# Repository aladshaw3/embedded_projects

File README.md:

## Personal Embedded Projects
Mono Repo for various personal embedded projects with my husband

This mono repo is strictly just for code development with a lot of boilerplate for helping
to write unit tests for the code. Does not include build instructions for specific devices.

# Getting Started

(1) Initial Setup

```bash
make environment
make grab-submodules
```

NOTE: Not strictly required if you have an environment that is already setup. See build/setup.sh for recommendations

(2) Running unit tests

```bash
make unit-tests
```

or

```bash
make unit-test TEST={TEST_NAME}
```

(3) Checking formatting

```bash
make static-code-analysis
make lint-filename
make pre-commit
```

or

```bash
make all-checks
```

(3) Building API-Docs

```bash
make api-docs
```

# Contributing

## New code project under `projects` folder

(1) Start by creating new folder under `projects`

e.g.,
```
embedded_projects/
├── projects/
│   ├── ExampleProject/
│   └── NewProject/         # Add here
```

(2) Update the `projects/sources.cmake` and `include.cmake` files for new location

e.g., source.cmake
```
################# Add other project directories here #####################
include_sources(ExampleProject)
include_sources(NewProject)      # Add here
```

e.g., include.cmake
```
################# Add other project directories here #####################
include_directories(${SIL_DIR}/ExampleProject)
include_directories(${SIL_DIR}/NewProject)
```

(3) Adding subdirectories in your project

You can add any subdirectories to your new project folder. You will
then need to add another layer of a `sources.cmake` file to add the
new subdirectories to be discoverable by the unit testing and static
code analysis infrastructure

See `projects/ExampleProject` for an example.

(4) Adding source code

Each sub-folder should contain both the header file and source file together.
Each sub-folder that contains source files needs to also include a `sources.cmake`
file. This file should call an `add_sources` helper function to tell cmake what
source files to include in the builds.

e.g., `projects/ExampleProject/unit_tests/sources.cmake`
```
add_sources(test_builds.cpp)
add_sources(test_eigen.cpp)
```

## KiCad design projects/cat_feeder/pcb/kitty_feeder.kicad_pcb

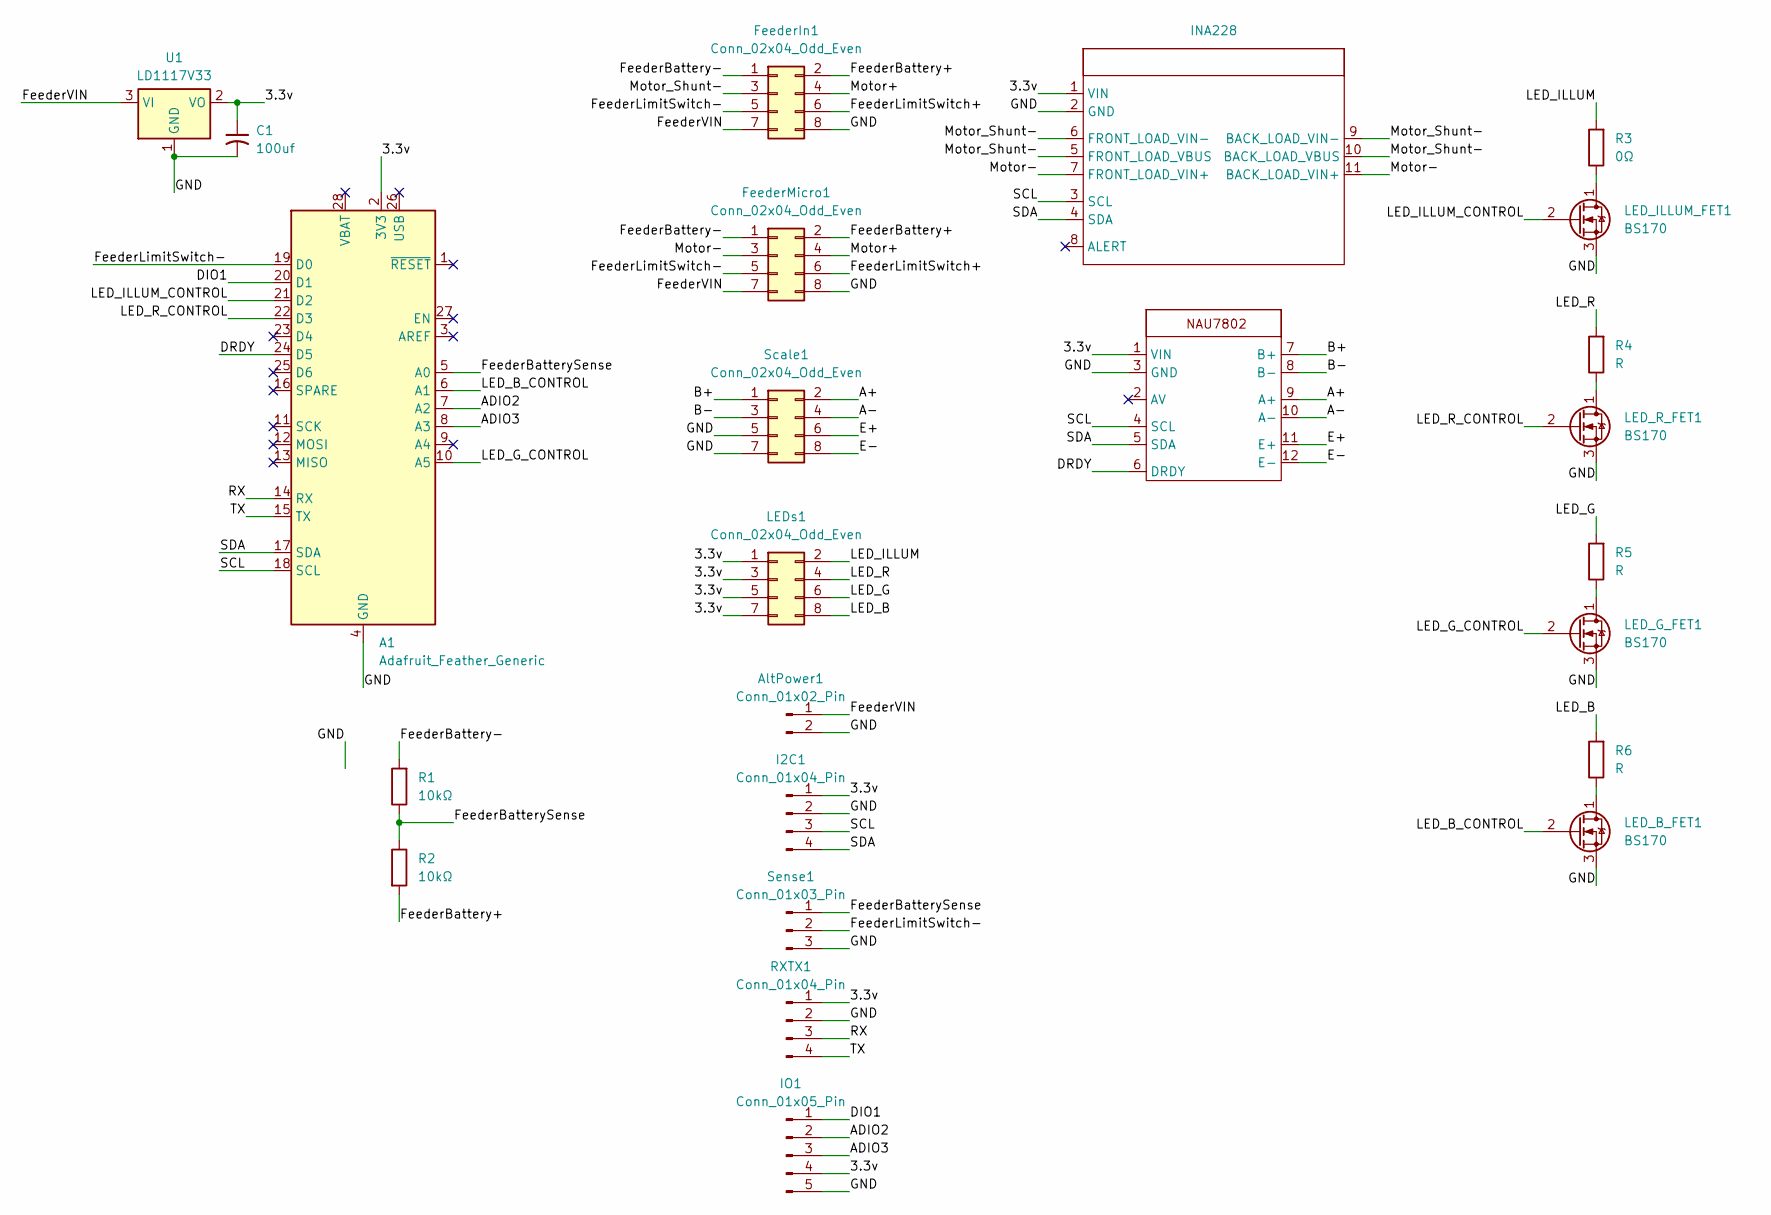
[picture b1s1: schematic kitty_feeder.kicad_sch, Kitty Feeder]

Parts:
A1: Adafruit_Feather_Generic; Adafruit_Feather
AltPower1: Conn_01x02_Pin; PinHeader_1x02_P2.54mm_Vertical
C1: 100uf; C_Radial_D6.3mm_H11.0mm_P2.50mm
FeederIn1: Conn_02x04_Odd_Even; PinHeader_2x04_P2.54mm_Vertical
FeederMicro1: Conn_02x04_Odd_Even; PinHeader_2x04_P2.54mm_Vertical
I2C1: Conn_01x04_Pin; PinHeader_1x04_P2.54mm_Vertical
INA228: ina228_module
IO1: Conn_01x05_Pin; PinHeader_1x05_P2.54mm_Vertical
LED_B_FET1: BS170; TO-92_Inline
LED_G_FET1: BS170; TO-92_Inline
LED_ILLUM_FET1: BS170; TO-92_Inline
LED_R_FET1: BS170; TO-92_Inline
LEDs1: Conn_02x04_Odd_Even; PinHeader_2x04_P2.54mm_Vertical
R1, R2: 10kΩ; R_Axial_DIN0207_L6.3mm_D2.5mm_P5.08mm_Vertical
R3: 0Ω; R_Axial_DIN0207_L6.3mm_D2.5mm_P5.08mm_Vertical
R4, R5, R6: R; R_Axial_DIN0207_L6.3mm_D2.5mm_P5.08mm_Vertical
RXTX1: Conn_01x04_Pin; PinHeader_1x04_P2.54mm_Vertical
Scale1: Conn_02x04_Odd_Even; PinHeader_2x04_P2.54mm_Vertical
Sense1: Conn_01x03_Pin; PinHeader_1x03_P2.54mm_Vertical
U1: LD1117V33; TO-220-3_Vertical
U2: nau7802_module

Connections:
/kitty_feeder/3.3v: A1.2 (3V3), C1.1, I2C1.1, INA228.1 (VIN), IO1.4, LEDs1.1, LEDs1.3, LEDs1.5, LEDs1.7, RXTX1.1, U1.2 (VO), U2.1 (VIN)
/kitty_feeder/A+: Scale1.2, U2.9 (A+)
/kitty_feeder/A-: Scale1.4, U2.10 (A-)
/kitty_feeder/ADIO2: A1.7 (A2), IO1.2
/kitty_feeder/ADIO3: A1.8 (A3), IO1.3
/kitty_feeder/B+: Scale1.1, U2.7 (B+)
/kitty_feeder/B-: Scale1.3, U2.8 (B-)
/kitty_feeder/DIO1: A1.20 (D1), IO1.1
/kitty_feeder/DRDY: A1.24 (D5), U2.6 (DRDY)
/kitty_feeder/E+: Scale1.6, U2.11 (E+)
/kitty_feeder/E-: Scale1.8, U2.12 (E-)
/kitty_feeder/FeederBattery+: FeederIn1.2, FeederMicro1.2, R2.2
/kitty_feeder/FeederBattery-: FeederIn1.1, FeederMicro1.1, R1.2
/kitty_feeder/FeederBatterySense: A1.5 (A0), R1.1, R2.1, Sense1.1
/kitty_feeder/FeederLimitSwitch+: FeederIn1.6, FeederMicro1.6
/kitty_feeder/FeederLimitSwitch-: A1.19 (D0), FeederIn1.5, FeederMicro1.5, Sense1.2
/kitty_feeder/FeederVIN: AltPower1.1, FeederIn1.7, FeederMicro1.7, U1.3 (VI)
/kitty_feeder/GND: A1.4 (GND), AltPower1.2, C1.2, FeederIn1.8, FeederMicro1.8, I2C1.2, INA228.2 (GND), IO1.5, LED_B_FET1.3 (S), LED_G_FET1.3 (S), LED_ILLUM_FET1.3 (S), LED_R_FET1.3 (S), RXTX1.2, Scale1.5, Scale1.7, Sense1.3, U1.1 (GND), U2.3 (GND)
/kitty_feeder/LED_B: LEDs1.8, R6.2
/kitty_feeder/LED_B_CONTROL: A1.6 (A1), LED_B_FET1.2 (G)
/kitty_feeder/LED_G: LEDs1.6, R5.2
/kitty_feeder/LED_G_CONTROL: A1.10 (A5), LED_G_FET1.2 (G)
/kitty_feeder/LED_ILLUM: LEDs1.2, R3.2
/kitty_feeder/LED_ILLUM_CONTROL: A1.21 (D2), LED_ILLUM_FET1.2 (G)
/kitty_feeder/LED_R: LEDs1.4, R4.2
/kitty_feeder/LED_R_CONTROL: A1.22 (D3), LED_R_FET1.2 (G)
/kitty_feeder/Motor+: FeederIn1.4, FeederMicro1.4
/kitty_feeder/Motor-: FeederMicro1.3, INA228.7 (FRONT_LOAD_VIN+), INA228.11 (BACK_LOAD_VIN+)
/kitty_feeder/Motor_Shunt-: FeederIn1.3, INA228.5 (FRONT_LOAD_VBUS), INA228.6 (FRONT_LOAD_VIN-), INA228.9 (BACK_LOAD_VIN-), INA228.10 (BACK_LOAD_VBUS)
/kitty_feeder/RX: A1.14 (RX), RXTX1.3
/kitty_feeder/SCL: A1.18 (SCL), I2C1.3, INA228.3 (SCL), U2.4 (SCL)
/kitty_feeder/SDA: A1.17 (SDA), I2C1.4, INA228.4 (SDA), U2.5 (SDA)
/kitty_feeder/TX: A1.15 (TX), RXTX1.4
unnamed: LED_B_FET1.1 (D), R6.1
unnamed: LED_G_FET1.1 (D), R5.1
unnamed: LED_ILLUM_FET1.1 (D), R3.1
unnamed: LED_R_FET1.1 (D), R4.1

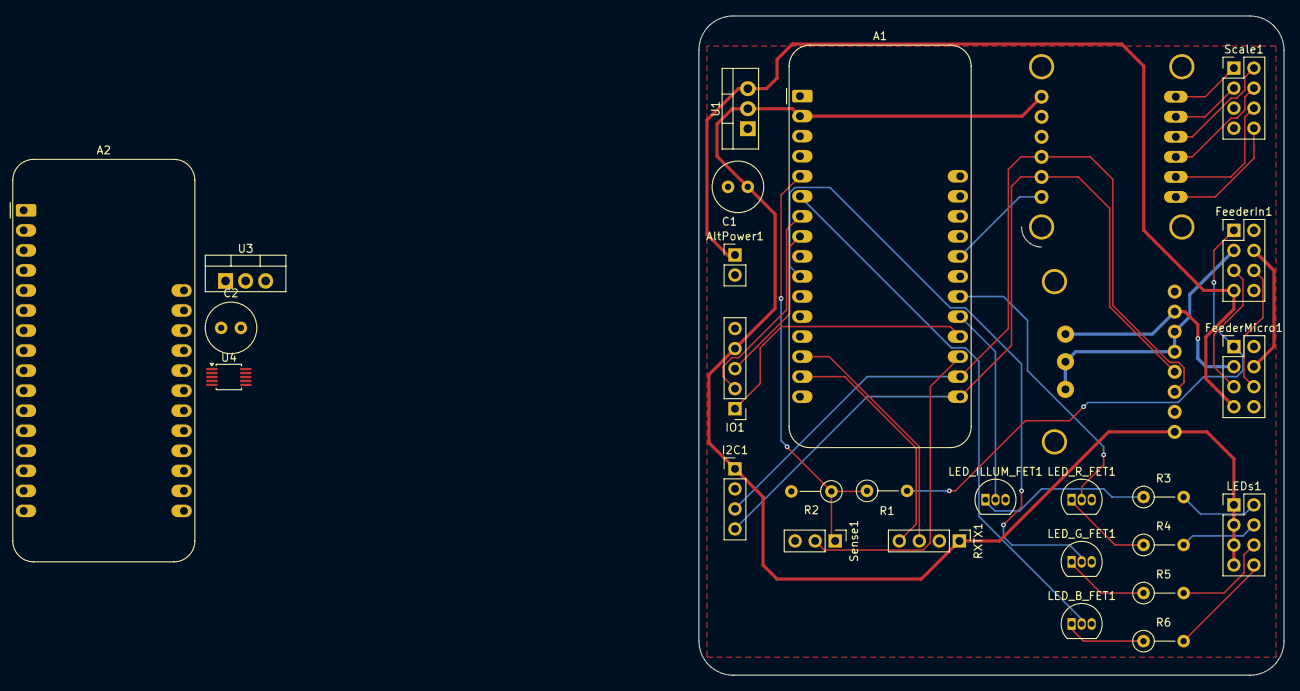
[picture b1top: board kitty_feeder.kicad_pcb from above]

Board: 2 copper layers, 74.2 x 83.6 mm, 28 parts (0 on the bottom side), 39 nets.

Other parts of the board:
A2: Adafruit_Feather_Generic; Adafruit_Feather
C2: C_Small_US; C_Radial_D6.3mm_H11.0mm_P2.50mm
U3: LD1117V33; TO-220-3_Vertical
U4: INA228; TSSOP-10_3x3mm_P0.5mm

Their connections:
/kitty_feeder_no_modules/3.3v: A2.2 (3V3), C2.1, U3.2 (VO)
/kitty_feeder_no_modules/GND: C2.2, U3.1 (GND)
